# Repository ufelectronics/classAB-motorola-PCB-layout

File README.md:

# classAB-motorola-PCB-layout

A PCB layout for making a experimental version yourself

# Motorola BJT Amp - Free KiCad Downloads

Build and experiment with the Motorola BJT Amp discussed on my profile back in November and December.

If you missed it, I once shared the KiCad file for simulating the Motorola AN-484A transistor amplifier.

Now I'm sharing the KiCad files for making a PCB yourself.

A The PCB includes:

* Integration of variable resistors (trimpots) - Make optimizations during testing - Faster results.

* Plenty of space around the components - Easier to measure at various points during testing.

* Through‑hole design, which makes it less demanding to build and therefore experiment‑ and beginner‑friendly.

* Schematic-Synchronized PCB Design - PCB design as it looks in the schematic, for easy mental switching.

This should guarantee easy experimentation, a fast outcome and way more fun. - An experience you'll never forget!

PRO TIP:

Use female pin headers at critical places instead of soldering the components directly onto the board. - This makes changes even easier and faster.

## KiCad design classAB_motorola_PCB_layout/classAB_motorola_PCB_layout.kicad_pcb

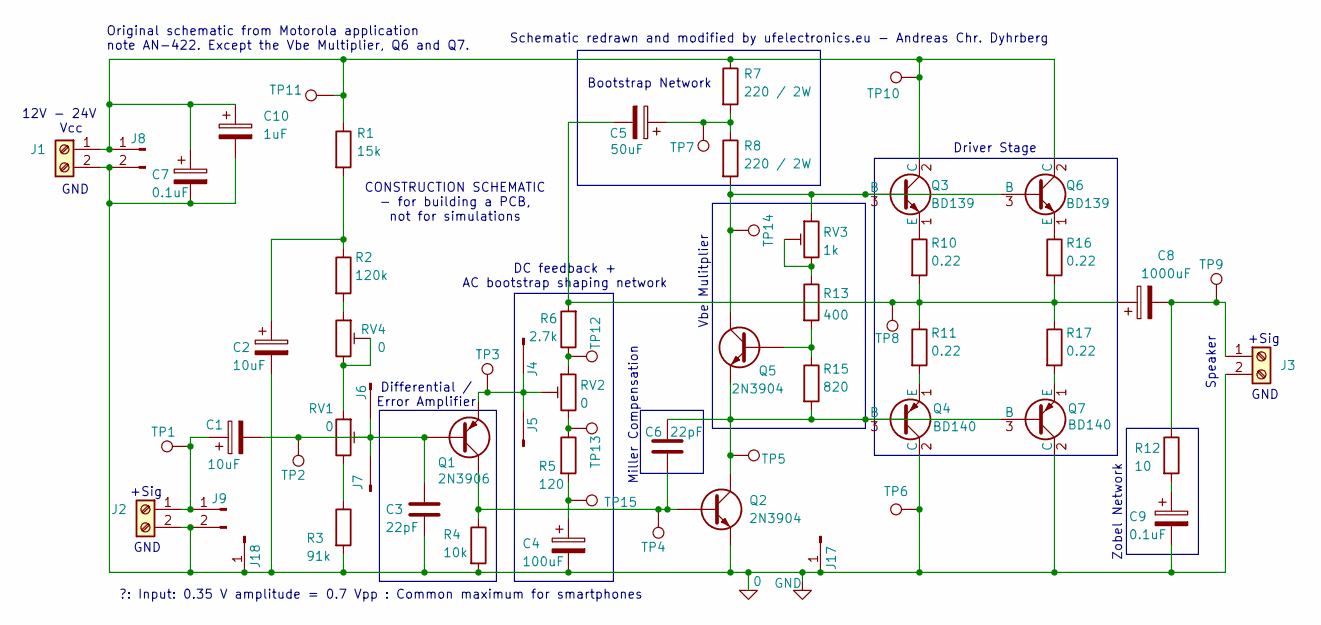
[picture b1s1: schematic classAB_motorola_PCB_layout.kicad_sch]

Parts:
C1, C2: 10uF; CP_Radial_D8.0mm_P5.00mm
C3, C6: 22pF; C_Disc_D7.5mm_W5.0mm_P10.00mm
C4: 100uF; CP_Radial_D8.0mm_P5.00mm
C5: 50uF; CP_Radial_D8.0mm_P5.00mm
C7: 0.1uF; CP_Radial_D8.0mm_P5.00mm
C8: 1000uF; C_Radial_D18.0mm_H35.5mm_P7.50mm
C9: 0.1uF; C_Disc_D7.5mm_W5.0mm_P10.00mm
C10: 1uF; CP_Radial_D8.0mm_P5.00mm
J1, J2, J3: Screw_Terminal_01x02; TerminalBlock_Phoenix_MKDS-1,5-2-5.08_1x02_P5.08mm_Horizont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
J4, J5, J6, J7, J17, J18: Conn_01x01_Pin; PinHeader_1x01_P2.54mm_Vertical
J8, J9: Conn_01x02_Pin; PinSocket_1x02_P2.54mm_Vertical
Q1: 2N3906; TO-92_Wide
Q2, Q5: 2N3904; TO-92_Wide
Q3, Q6: BD139; SOT-32_STM
Q4, Q7: BD140; SOT-32_STM
R1: 15k; R_Axial_DIN0411_L9.9mm_D3.6mm_P15.24mm_Horizontal
R2: 120k; R_Axial_DIN0411_L9.9mm_D3.6mm_P15.24mm_Horizontal
R3: 91k; R_Axial_DIN0411_L9.9mm_D3.6mm_P15.24mm_Horizontal
R4: 10k; R_Axial_DIN0411_L9.9mm_D3.6mm_P15.24mm_Horizontal
R5: 120; R_Axial_DIN0411_L9.9mm_D3.6mm_P15.24mm_Horizontal
R6: 2.7k; R_Axial_DIN0411_L9.9mm_D3.6mm_P15.24mm_Horizontal
R7, R8: 220 / 2W; R_Axial_DIN0411_L9.9mm_D3.6mm_P15.24mm_Horizontal
R10, R11, R16, R17: 0.22; R_Axial_DIN0614_L14.3mm_D5.7mm_P25.40mm_Horizontal
R12: 10; R_Axial_DIN0614_L14.3mm_D5.7mm_P25.40mm_Horizontal
R13: 400; R_Axial_DIN0411_L9.9mm_D3.6mm_P15.24mm_Horizontal
R15: 820; R_Axial_DIN0411_L9.9mm_D3.6mm_P15.24mm_Horizontal
RV1, RV2, RV4: 0; Potentiometer_Bourns_3266Y_Vertical
RV3: 1k; Potentiometer_Bourns_3266Y_Vertical
TP1, TP2, TP3, TP4, TP5, TP6, TP7, TP8, TP9, TP10, TP11, TP12, TP13, TP14, TP15: TestPoint; TestPoint_Pad_D1.5mm

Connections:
0: C2.2, C3.2, C4.2, C7.2, C9.2, C10.2, J1.2, J2.2, J3.2, J8.2, J9.2, J17.1, J18.1, Q2.3 (E), Q4.2 (C), Q7.2 (C), R3.2, R4.2, TP6.1
unnamed: C2.1, R1.2, R2.1
unnamed: C4.1, R5.2, TP15.1
unnamed: C5.1, R7.2, R8.1, TP7.1
unnamed: C5.2, C8.1, R6.2, R10.2, R11.1, R16.2, R17.1, TP8.1
unnamed: C9.1, R12.2
unnamed: C7.1, C10.1, J1.1, J8.1, Q3.2 (C), Q6.2 (C), R1.1, R7.1, TP10.1, TP11.1
unnamed: C1.1, J2.1, J9.1, TP1.1
unnamed: C8.2, J3.1, R12.1, TP9.1
unnamed: J4.1, J5.1, Q1.3 (E), RV2.2, TP3.1
unnamed: C1.2, C3.1, J6.1, J7.1, Q1.2 (B), RV1.2, TP2.1
unnamed: C6.2, Q1.1 (C), Q2.2 (B), R4.1, TP4.1
unnamed: C6.1, Q2.1 (C), Q4.3 (B), Q5.3 (E), Q7.3 (B), R15.2, TP5.1
unnamed: Q3.3 (B), Q5.1 (C), Q6.3 (B), R8.2, RV3.1, TP14.1
unnamed: Q3.1 (E), R10.1
unnamed: Q4.1 (E), R11.2
unnamed: Q5.2 (B), R13.2, R15.1
unnamed: Q6.1 (E), R16.1
unnamed: Q7.1 (E), R17.2
unnamed: R2.2, RV4.1
unnamed: R3.1, RV1.3
unnamed: R5.1, RV2.3, TP13.1
unnamed: R6.1, RV2.1, TP12.1
unnamed: R13.1, RV3.2, RV3.3
unnamed: RV1.1, RV4.2, RV4.3

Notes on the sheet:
GND
Zobel Network
?: Input: 0.35 V amplitude = 0.7 Vpp : Common maximum for smartphones
12V - 24V
+Sig
Bootstrap Network
Miller Compensation
Vcc
Differential / Error Amplifier
Speaker
CONSTRUCTION SCHEMATIC - for building a PCB, not for simulations
Original schematic from Motorola application note AN-422. Except the Vbe Multiplier, Q6 and Q7.
DC feedback + AC bootstrap shaping network
Vbe Mulitplier
Schematic redrawn and modified by ufelectronics.eu - Andreas Chr. Dyhrberg
Driver Stage

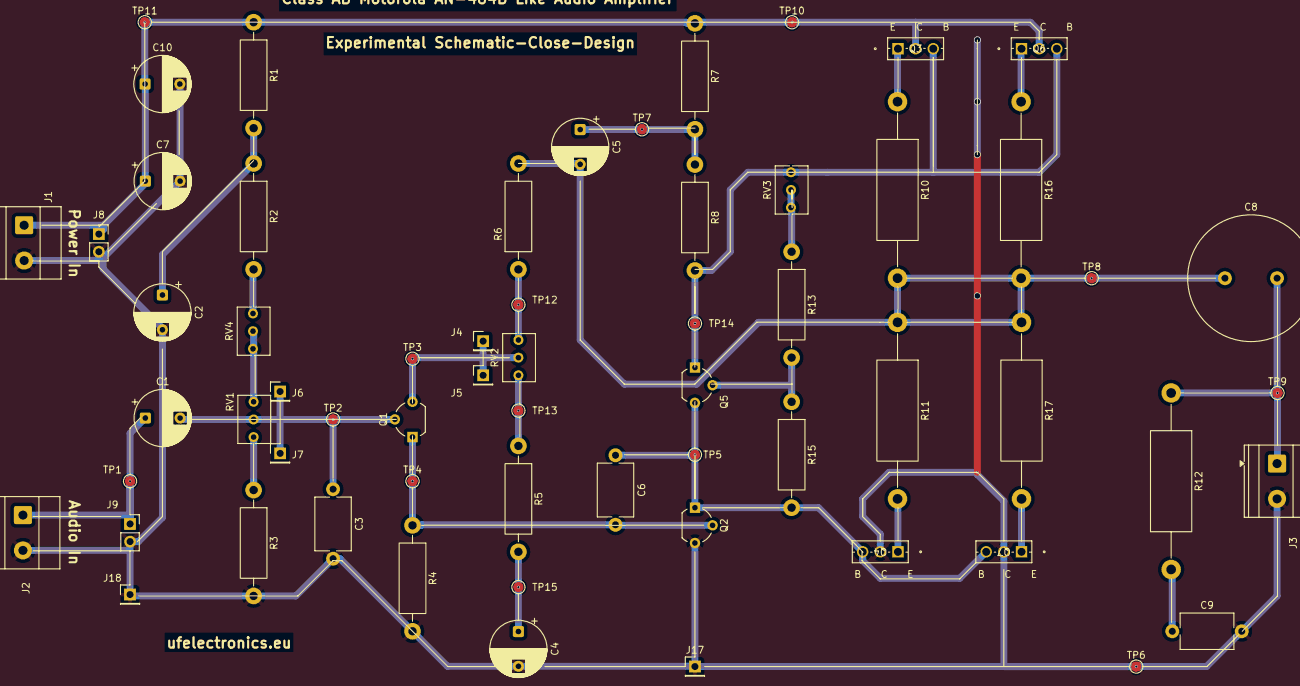
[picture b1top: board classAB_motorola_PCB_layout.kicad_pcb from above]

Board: 2 copper layers, 62 parts (0 on the bottom side), 25 nets.

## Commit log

2026-01-19 Extended the readme file.
2026-01-19 Added example of pin header use.
